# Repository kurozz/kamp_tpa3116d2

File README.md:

# KAmp

Audio amplifier based on the evaluation module from Texas Instruments.

It should be able to drive 2 speakers at a max of 50W each or a single speaker at a max of 100W (PBTL). Minimal changes are need to change to PBTL.

Multiple devices can be chained together using the Sync connectors. One device should be made Master while the others should operate as Slave devices.

This is not finished and not tested. Will keep updating if I feel like it.

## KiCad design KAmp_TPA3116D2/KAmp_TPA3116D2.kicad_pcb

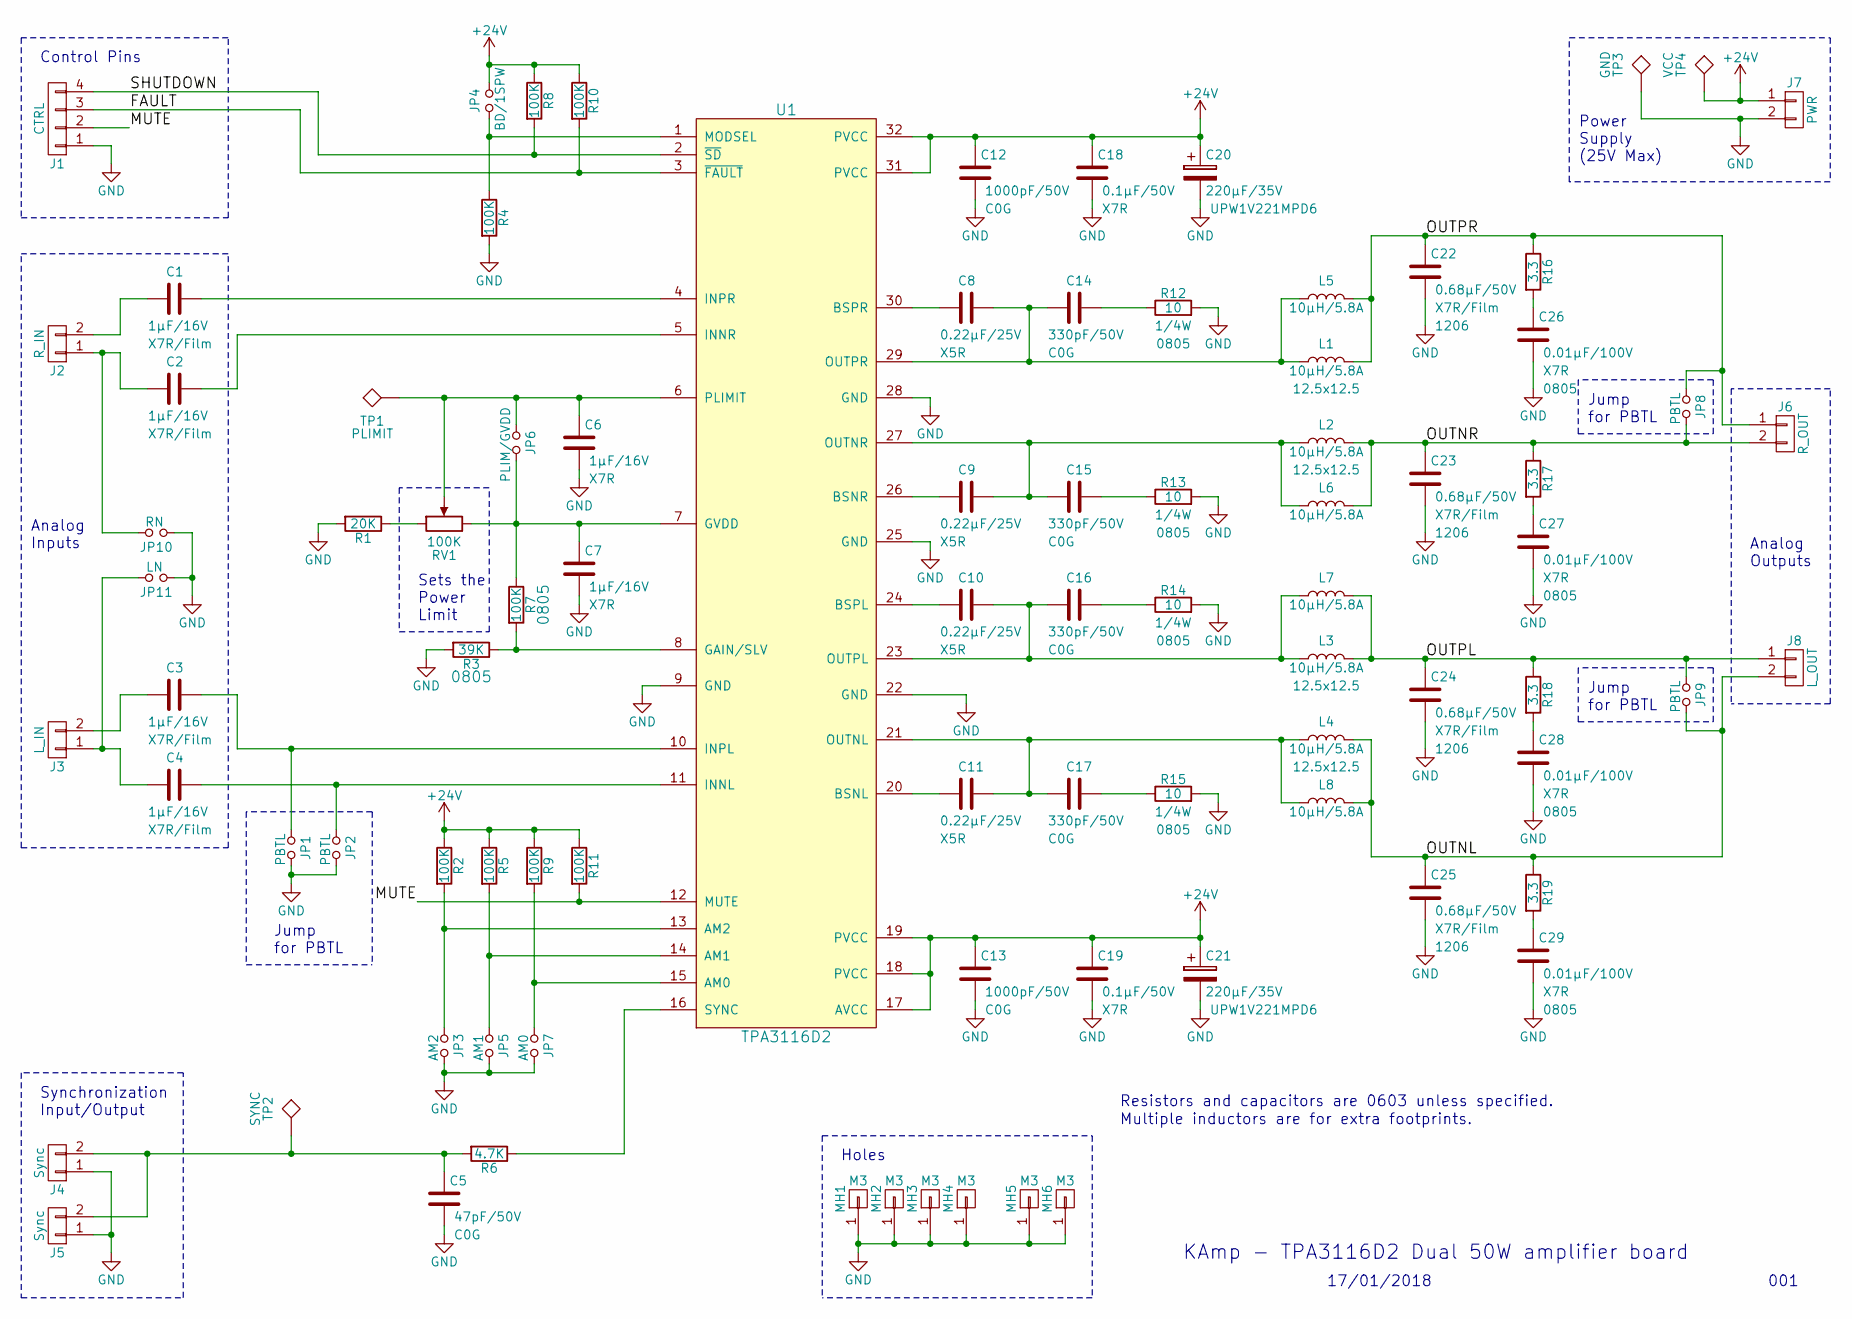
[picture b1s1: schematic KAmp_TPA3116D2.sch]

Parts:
C1, C2, C3, C4: 1µF/16V; C_0603; Rating X7R/Film
C5: 47pF/50V; C_0603; Rating C0G
C6, C7: 1µF/16V; C_0603; Rating X7R
C8, C9, C10, C11: 0.22µF/25V; C_0603; Rating X5R
C12, C13: 1000pF/50V; C_0603; Rating C0G
C14, C15, C16, C17: 330pF/50V; C_0603; Rating C0G
C18, C19: 0.1µF/50V; C_0603; Rating X7R
C20, C21: 220µF/35V; CP_Radial_D8.0mm_P3.50mm
C22, C23, C24, C25: 0.68µF/50V; C_1206; Rating X7R/Film
C26, C27, C28, C29: 0.01µF/100V; C_0805; Rating X7R
J1: CTRL; JST_EH_B04B-EH-A_04x2.50mm_Straight
J2: R_IN; JST_EH_B02B-EH-A_02x2.50mm_Straight
J3: L_IN; JST_EH_B02B-EH-A_02x2.50mm_Straight
J4, J5: Sync; JST_EH_B02B-EH-A_02x2.50mm_Straight
J6: R_OUT; TerminalBlock_bornier-2_P5.08mm
J7: PWR; TerminalBlock_bornier-2_P5.08mm
J8: L_OUT; TerminalBlock_bornier-2_P5.08mm
JP1, JP2: PBTL; Pin_Header_Straight_1x02_Pitch2.54mm
JP3: AM2; R_0603
JP4: BD/1SPW; R_0603
JP5: AM1; R_0603
JP6: PLIM/GVDD; R_0603
JP7: AM0; R_0603
JP8, JP9: PBTL; R_Axial_DIN0204_L3.6mm_D1.6mm_P5.08mm_Horizontal
JP10: RN; R_0603
JP11: LN; R_0603
L1, L2, L3, L4: 10µH/5.8A; Choke_SMD_12x12mm_h8mm
L5, L6, L7, L8: 10µH/5.8A; L_Toroid_Horizontal_D11.2mm_P17.00mm_Diameter12-5mm_Amidon-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
MH1, MH2, MH3, MH4: M3; MountingHole_3.2mm_M3_Pad_Via
MH5, MH6: M3; MountingHole_3.2mm_M3_Pad
R1: 20K; R_0603
R2, R4, R5, R8, R9, R10, R11: 100K; R_0603
R3: 39K; R_0805
R6: 4.7K; R_0603
R7: 100K; R_0805
R12, R13, R14, R15: 10; R_0805
R16, R17, R18, R19: 3.3; R_0603
RV1: 100K; Potentiometer_Trimmer-EVM3E
TP1: PLIMIT; Test_Point
TP2: SYNC; Test_Point
TP3: GND; Test_Point
TP4: VCC; Test_Point
U1: TPA3116D2; HTSSOP-32_6.1x11mm_Pitch0.65mm_ThermalPad

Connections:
+24V: C12.1, C13.1, C18.1, C19.1, C20.1, C21.1, J7.1, JP4.2, R2.1, R5.1, R8.1, R9.1, R10.1, R11.1, TP4.1, U1.17 (AVCC), U1.18 (PVCC), U1.19 (PVCC), U1.31 (PVCC), U1.32 (PVCC)
/FAULT: J1.3, R10.2, U1.3 (~FAULT)
/MUTE: J1.2, R11.2, U1.12 (MUTE)
/OUTNL: C25.1, J8.2, JP9.2, L4.2, L8.2, R19.1
/OUTNR: C23.1, J6.2, JP8.2, L2.2, L6.2, R17.1
/OUTPL: C24.1, J8.1, JP9.1, L3.2, L7.2, R18.1
/OUTPR: C22.1, J6.1, JP8.1, L1.2, L5.2, R16.1
/SHUTDOWN: J1.4, R8.2, U1.2 (~SD)
GND: C5.2, C6.2, C7.2, C12.2, C13.2, C18.2, C19.2, C20.2, C21.2, C22.2, C23.2, C24.2, C25.2, C26.2, C27.2, C28.2, C29.2, J1.1, J4.1, J5.1, J7.2, JP1.2, JP2.2, JP3.2, JP5.2, JP7.2, JP10.1, JP11.1, MH1.1, MH2.1, MH3.1, MH4.1, MH5.1, MH6.1, R1.2, R3.2, R4.2, R12.2, R13.2, R14.2, R15.2, TP3.1, U1.9 (GND), U1.22 (GND), U1.25 (GND), U1.28 (GND), U1.33 (GND)
unnamed: C1.1, U1.4 (INPR)
unnamed: C1.2, J2.2
unnamed: C2.1, U1.5 (INNR)
unnamed: C2.2, J2.1, JP10.2
unnamed: C3.1, JP1.1, U1.10 (INPL)
unnamed: C3.2, J3.2
unnamed: C4.1, JP2.1, U1.11 (INNL)
unnamed: C4.2, J3.1, JP11.2
unnamed: C5.1, J4.2, J5.2, R6.2, TP2.1
unnamed: C6.1, JP6.1, RV1.2, TP1.1, U1.6 (PLIMIT)
unnamed: C7.1, JP6.2, R7.1, RV1.3, U1.7 (GVDD)
unnamed: C8.2, U1.30 (BSPR)
unnamed: C9.2, U1.26 (BSNR)
unnamed: C10.1, C16.2, L3.1, L7.1, U1.23 (OUTPL)
unnamed: C10.2, U1.24 (BSPL)
unnamed: C11.1, C17.2, L4.1, L8.1, U1.21 (OUTNL)
unnamed: C11.2, U1.20 (BSNL)
unnamed: C14.1, R12.1
unnamed: C8.1, C14.2, L1.1, L5.1, U1.29 (OUTPR)
unnamed: C15.1, R13.1
unnamed: C9.1, C15.2, L2.1, L6.1, U1.27 (OUTNR)
unnamed: C16.1, R14.1
unnamed: C17.1, R15.1
unnamed: C26.1, R16.2
unnamed: C27.1, R17.2
unnamed: C28.1, R18.2
unnamed: C29.1, R19.2
unnamed: JP3.1, R2.2, U1.13 (AM2)
unnamed: JP4.1, R4.1, U1.1 (MODSEL)
unnamed: JP5.1, R5.2, U1.14 (AM1)
unnamed: JP7.1, R9.2, U1.15 (AM0)
unnamed: R1.1, RV1.1
unnamed: R3.1, R7.2, U1.8 (GAIN/SLV)
unnamed: R6.1, U1.16 (SYNC)

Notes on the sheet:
Synchronization Input/Output
Analog Inputs
Jump for PBTL
Control Pins
Power Supply (25V Max)
Analog Outputs
Sets the Power Limit
Holes
KAmp - TPA3116D2 Dual 50W amplifier board
17/01/2018
001
Resistors and capacitors are 0603 unless specified.
Multiple inductors are for extra footprints.

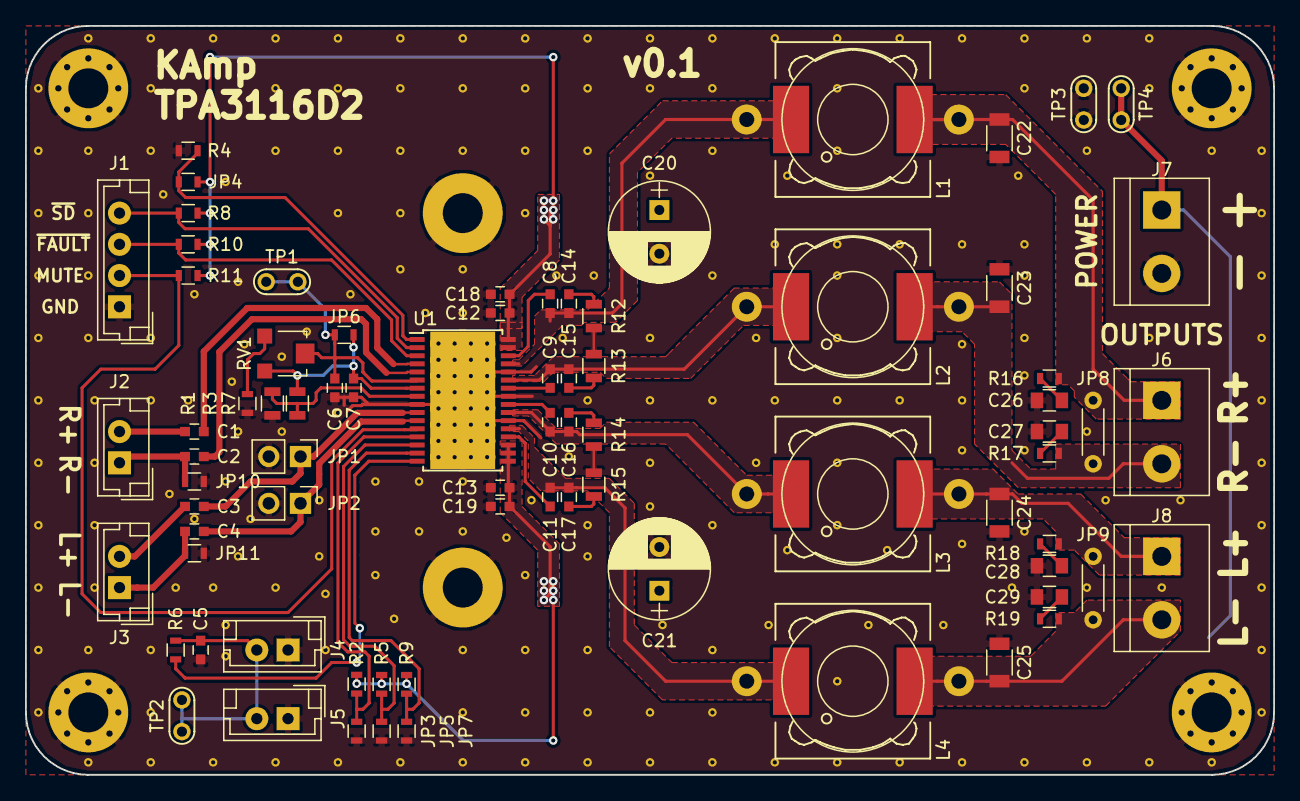
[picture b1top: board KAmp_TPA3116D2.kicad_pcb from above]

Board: 2 copper layers, 100.0 x 60.0 mm, 87 parts (0 on the bottom side), 43 nets.
